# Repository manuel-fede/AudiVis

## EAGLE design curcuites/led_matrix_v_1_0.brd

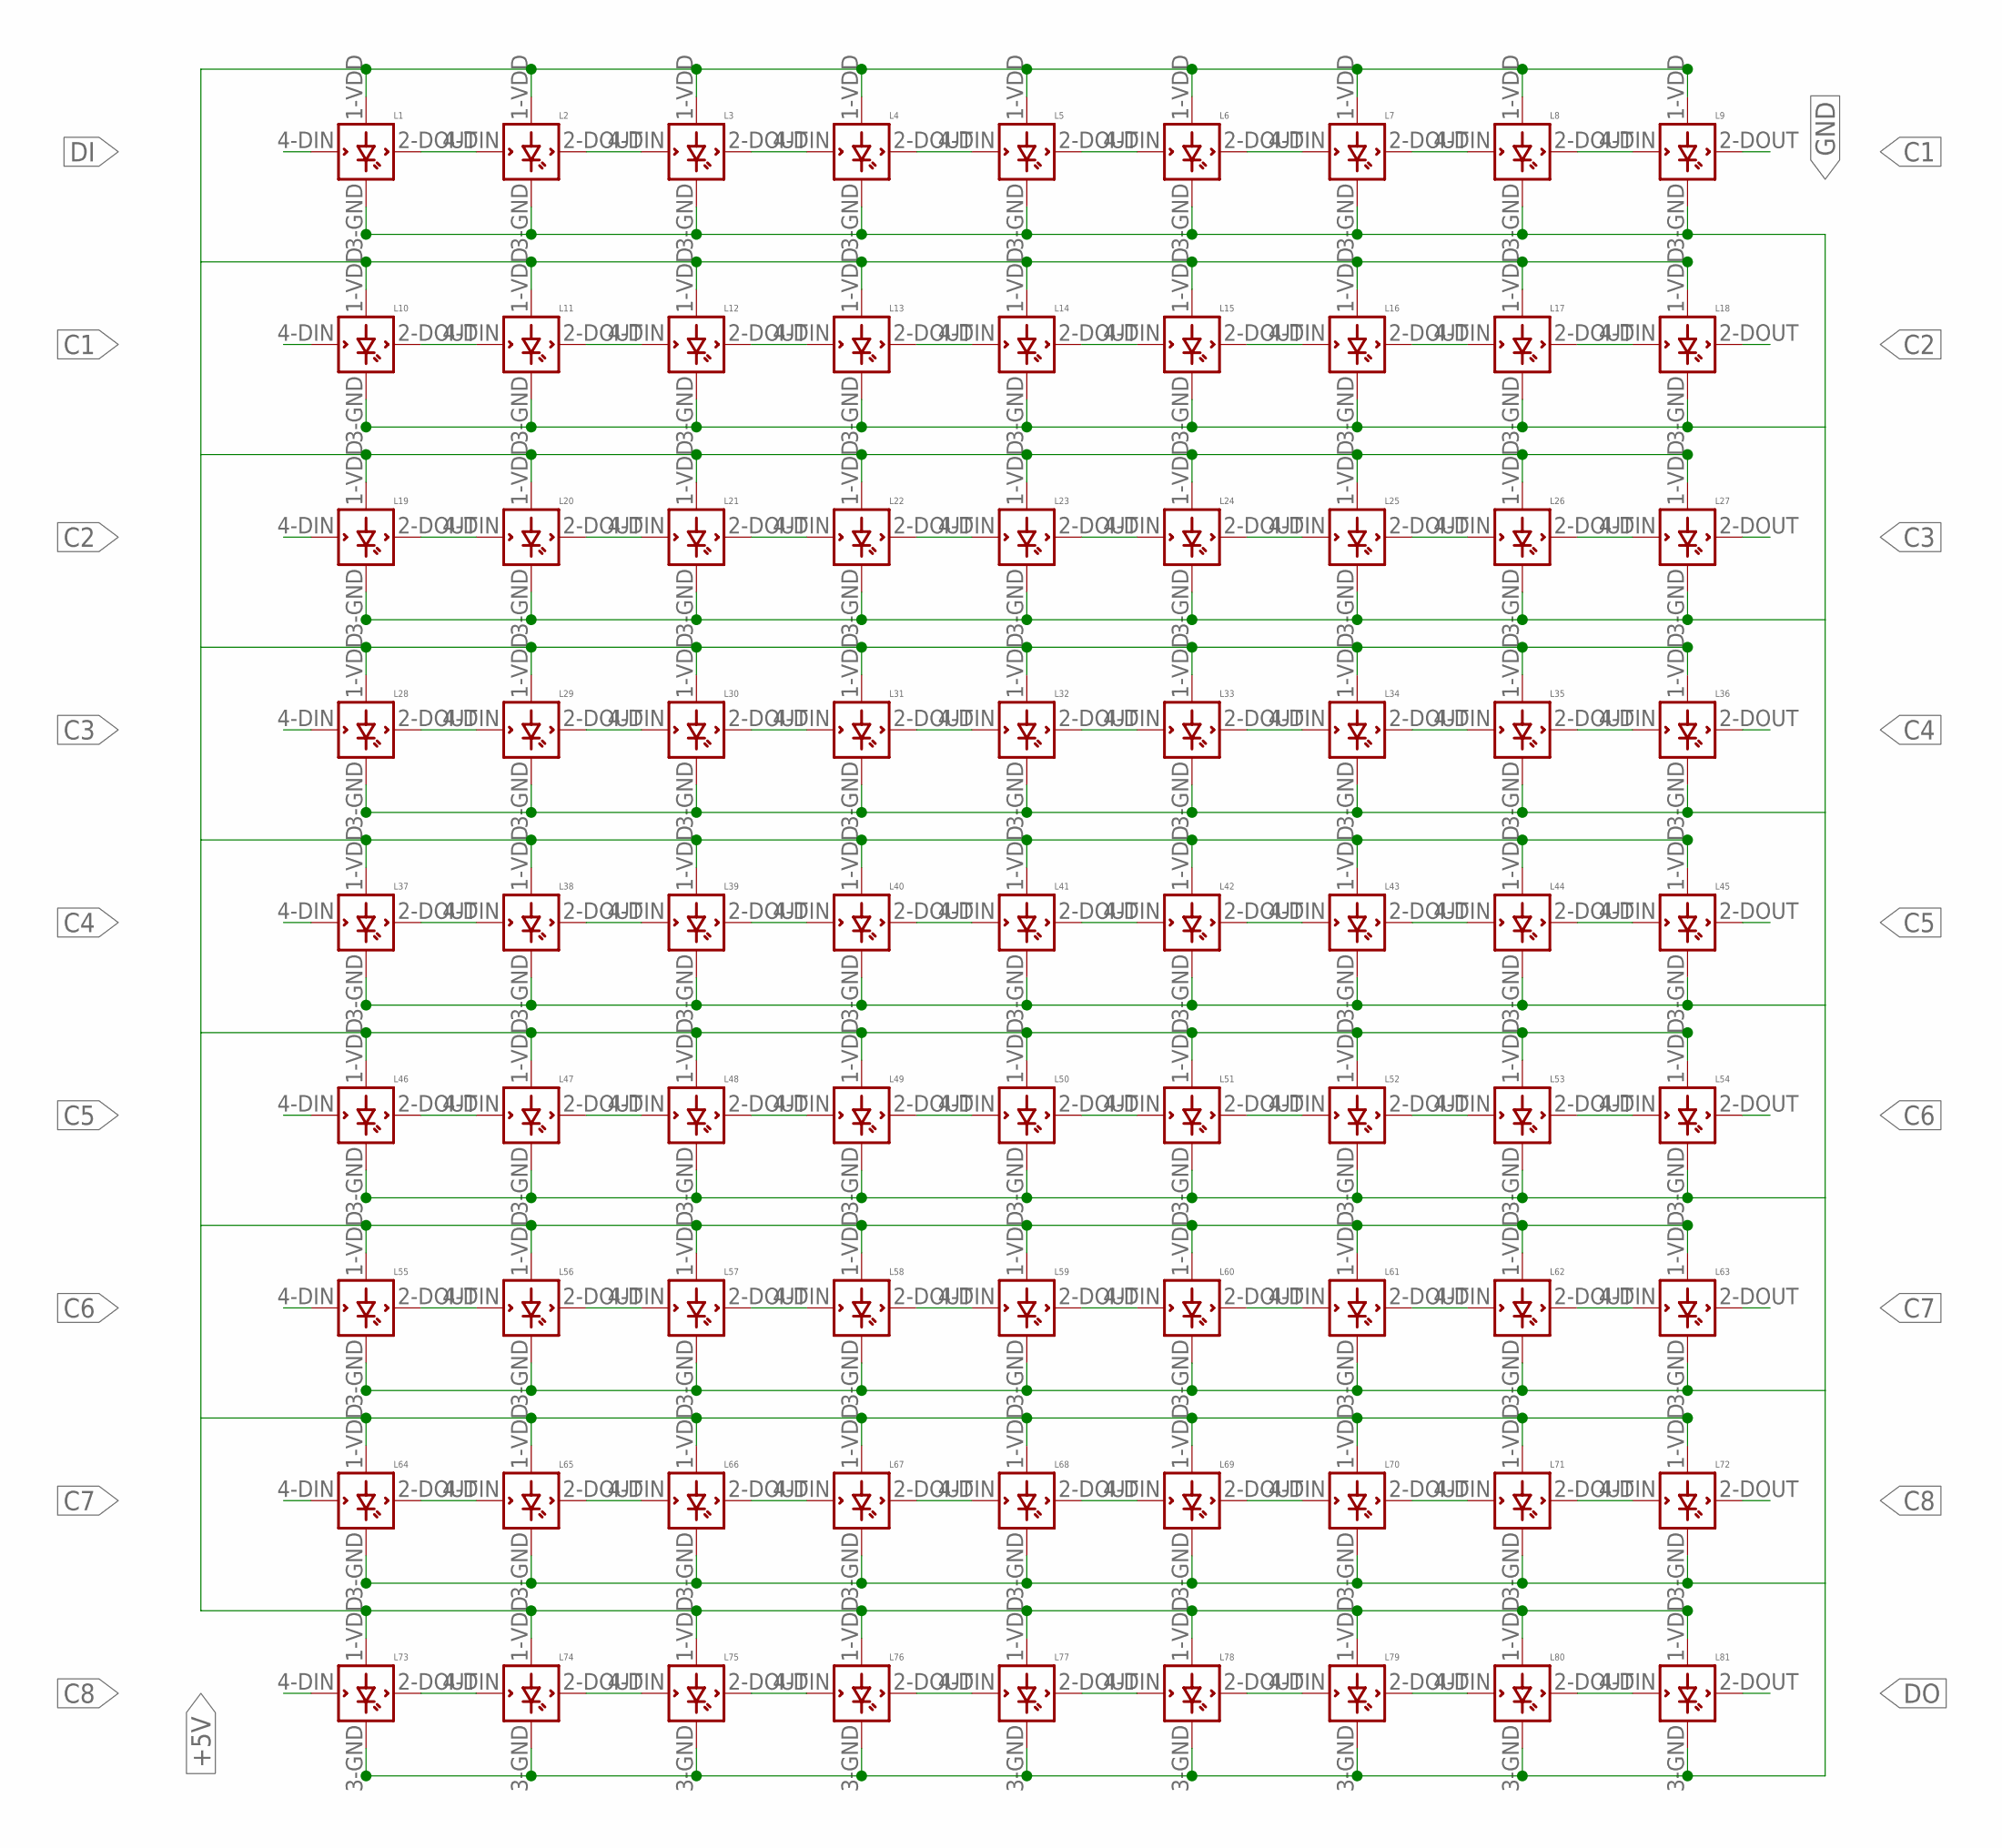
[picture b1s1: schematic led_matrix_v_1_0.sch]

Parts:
L1, L2, L3, L4, L5, L6, L7, L8, L9, L10, L11, L12, L13, L14, L15, L16, L17, L18, L19, L20, L21, L22, L23, L24, L25, L26, L27, L28, L29, L30, L31, L32, L33, L34, L35, L36, L37, L38, L39, L40, L41, L42, L43, L44, L45, L46, L47, L48, L49, L50, L51, L52, L53, L54, L55, L56, L57, L58, L59, L60, L61, L62, L63, L64, L65, L66, L67, L68, L69, L70, L71, L72, L73, L74, L75, L76, L77, L78, L79, L80, L81: WS2812B

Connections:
+5V: L1.1-VDD (VDD), L2.1-VDD (VDD), L3.1-VDD (VDD), L4.1-VDD (VDD), L5.1-VDD (VDD), L6.1-VDD (VDD), L7.1-VDD (VDD), L8.1-VDD (VDD), L9.1-VDD (VDD), L10.1-VDD (VDD), L11.1-VDD (VDD), L12.1-VDD (VDD), L13.1-VDD (VDD), L14.1-VDD (VDD), L15.1-VDD (VDD), L16.1-VDD (VDD), L17.1-VDD (VDD), L18.1-VDD (VDD), L19.1-VDD (VDD), L20.1-VDD (VDD), L21.1-VDD (VDD), L22.1-VDD (VDD), L23.1-VDD (VDD), L24.1-VDD (VDD), L25.1-VDD (VDD), L26.1-VDD (VDD), L27.1-VDD (VDD), L28.1-VDD (VDD), L29.1-VDD (VDD), L30.1-VDD (VDD), L31.1-VDD (VDD), L32.1-VDD (VDD), L33.1-VDD (VDD), L34.1-VDD (VDD), L35.1-VDD (VDD), L36.1-VDD (VDD), L37.1-VDD (VDD), L38.1-VDD (VDD), L39.1-VDD (VDD), L40.1-VDD (VDD), L41.1-VDD (VDD), L42.1-VDD (VDD), L43.1-VDD (VDD), L44.1-VDD (VDD), L45.1-VDD (VDD), L46.1-VDD (VDD), L47.1-VDD (VDD), L48.1-VDD (VDD), L49.1-VDD (VDD), L50.1-VDD (VDD), L51.1-VDD (VDD), L52.1-VDD (VDD), L53.1-VDD (VDD), L54.1-VDD (VDD), L55.1-VDD (VDD), L56.1-VDD (VDD), L57.1-VDD (VDD), L58.1-VDD (VDD), L59.1-VDD (VDD), L60.1-VDD (VDD), L61.1-VDD (VDD), L62.1-VDD (VDD), L63.1-VDD (VDD), L64.1-VDD (VDD), L65.1-VDD (VDD), L66.1-VDD (VDD), L67.1-VDD (VDD), L68.1-VDD (VDD), L69.1-VDD (VDD), L70.1-VDD (VDD), L71.1-VDD (VDD), L72.1-VDD (VDD), L73.1-VDD (VDD), L74.1-VDD (VDD), L75.1-VDD (VDD), L76.1-VDD (VDD), L77.1-VDD (VDD), L78.1-VDD (VDD), L79.1-VDD (VDD), L80.1-VDD (VDD), L81.1-VDD (VDD)
C1: L9.2-DOUT (DOUT), L10.4-DIN (DIN)
C2: L18.2-DOUT (DOUT), L19.4-DIN (DIN)
C3: L27.2-DOUT (DOUT), L28.4-DIN (DIN)
C4: L36.2-DOUT (DOUT), L37.4-DIN (DIN)
C5: L45.2-DOUT (DOUT), L46.4-DIN (DIN)
C6: L54.2-DOUT (DOUT), L55.4-DIN (DIN)
C7: L63.2-DOUT (DOUT), L64.4-DIN (DIN)
C8: L72.2-DOUT (DOUT), L73.4-DIN (DIN)
DI: L1.4-DIN (DIN)
DO: L81.2-DOUT (DOUT)
GND: L1.3-GND (GND), L2.3-GND (GND), L3.3-GND (GND), L4.3-GND (GND), L5.3-GND (GND), L6.3-GND (GND), L7.3-GND (GND), L8.3-GND (GND), L9.3-GND (GND), L10.3-GND (GND), L11.3-GND (GND), L12.3-GND (GND), L13.3-GND (GND), L14.3-GND (GND), L15.3-GND (GND), L16.3-GND (GND), L17.3-GND (GND), L18.3-GND (GND), L19.3-GND (GND), L20.3-GND (GND), L21.3-GND (GND), L22.3-GND (GND), L23.3-GND (GND), L24.3-GND (GND), L25.3-GND (GND), L26.3-GND (GND), L27.3-GND (GND), L28.3-GND (GND), L29.3-GND (GND), L30.3-GND (GND), L31.3-GND (GND), L32.3-GND (GND), L33.3-GND (GND), L34.3-GND (GND), L35.3-GND (GND), L36.3-GND (GND), L37.3-GND (GND), L38.3-GND (GND), L39.3-GND (GND), L40.3-GND (GND), L41.3-GND (GND), L42.3-GND (GND), L43.3-GND (GND), L44.3-GND (GND), L45.3-GND (GND), L46.3-GND (GND), L47.3-GND (GND), L48.3-GND (GND), L49.3-GND (GND), L50.3-GND (GND), L51.3-GND (GND), L52.3-GND (GND), L53.3-GND (GND), L54.3-GND (GND), L55.3-GND (GND), L56.3-GND (GND), L57.3-GND (GND), L58.3-GND (GND), L59.3-GND (GND), L60.3-GND (GND), L61.3-GND (GND), L62.3-GND (GND), L63.3-GND (GND), L64.3-GND (GND), L65.3-GND (GND), L66.3-GND (GND), L67.3-GND (GND), L68.3-GND (GND), L69.3-GND (GND), L70.3-GND (GND), L71.3-GND (GND), L72.3-GND (GND), L73.3-GND (GND), L74.3-GND (GND), L75.3-GND (GND), L76.3-GND (GND), L77.3-GND (GND), L78.3-GND (GND), L79.3-GND (GND), L80.3-GND (GND), L81.3-GND (GND)
unnamed: L10.2-DOUT (DOUT), L11.4-DIN (DIN)
unnamed: L2.2-DOUT (DOUT), L3.4-DIN (DIN)
unnamed: L3.2-DOUT (DOUT), L4.4-DIN (DIN)
unnamed: L11.2-DOUT (DOUT), L12.4-DIN (DIN)
unnamed: L4.2-DOUT (DOUT), L5.4-DIN (DIN)
unnamed: L12.2-DOUT (DOUT), L13.4-DIN (DIN)
unnamed: L1.2-DOUT (DOUT), L2.4-DIN (DIN)
unnamed: L5.2-DOUT (DOUT), L6.4-DIN (DIN)
unnamed: L6.2-DOUT (DOUT), L7.4-DIN (DIN)
unnamed: L7.2-DOUT (DOUT), L8.4-DIN (DIN)
unnamed: L8.2-DOUT (DOUT), L9.4-DIN (DIN)
unnamed: L13.2-DOUT (DOUT), L14.4-DIN (DIN)
unnamed: L14.2-DOUT (DOUT), L15.4-DIN (DIN)
unnamed: L15.2-DOUT (DOUT), L16.4-DIN (DIN)
unnamed: L16.2-DOUT (DOUT), L17.4-DIN (DIN)
unnamed: L17.2-DOUT (DOUT), L18.4-DIN (DIN)
unnamed: L19.2-DOUT (DOUT), L20.4-DIN (DIN)
unnamed: L20.2-DOUT (DOUT), L21.4-DIN (DIN)
unnamed: L21.2-DOUT (DOUT), L22.4-DIN (DIN)
unnamed: L22.2-DOUT (DOUT), L23.4-DIN (DIN)
unnamed: L23.2-DOUT (DOUT), L24.4-DIN (DIN)
unnamed: L24.2-DOUT (DOUT), L25.4-DIN (DIN)
unnamed: L25.2-DOUT (DOUT), L26.4-DIN (DIN)
unnamed: L26.2-DOUT (DOUT), L27.4-DIN (DIN)
unnamed: L28.2-DOUT (DOUT), L29.4-DIN (DIN)
unnamed: L29.2-DOUT (DOUT), L30.4-DIN (DIN)
unnamed: L30.2-DOUT (DOUT), L31.4-DIN (DIN)
unnamed: L31.2-DOUT (DOUT), L32.4-DIN (DIN)
unnamed: L32.2-DOUT (DOUT), L33.4-DIN (DIN)
unnamed: L33.2-DOUT (DOUT), L34.4-DIN (DIN)
unnamed: L34.2-DOUT (DOUT), L35.4-DIN (DIN)
unnamed: L35.2-DOUT (DOUT), L36.4-DIN (DIN)
unnamed: L37.2-DOUT (DOUT), L38.4-DIN (DIN)
unnamed: L38.2-DOUT (DOUT), L39.4-DIN (DIN)
unnamed: L39.2-DOUT (DOUT), L40.4-DIN (DIN)
unnamed: L40.2-DOUT (DOUT), L41.4-DIN (DIN)
unnamed: L41.2-DOUT (DOUT), L42.4-DIN (DIN)
unnamed: L42.2-DOUT (DOUT), L43.4-DIN (DIN)
unnamed: L43.2-DOUT (DOUT), L44.4-DIN (DIN)
unnamed: L44.2-DOUT (DOUT), L45.4-DIN (DIN)
unnamed: L46.2-DOUT (DOUT), L47.4-DIN (DIN)
unnamed: L47.2-DOUT (DOUT), L48.4-DIN (DIN)
unnamed: L48.2-DOUT (DOUT), L49.4-DIN (DIN)
unnamed: L49.2-DOUT (DOUT), L50.4-DIN (DIN)
unnamed: L50.2-DOUT (DOUT), L51.4-DIN (DIN)
unnamed: L51.2-DOUT (DOUT), L52.4-DIN (DIN)
unnamed: L52.2-DOUT (DOUT), L53.4-DIN (DIN)
unnamed: L53.2-DOUT (DOUT), L54.4-DIN (DIN)
unnamed: L55.2-DOUT (DOUT), L56.4-DIN (DIN)
unnamed: L56.2-DOUT (DOUT), L57.4-DIN (DIN)
unnamed: L57.2-DOUT (DOUT), L58.4-DIN (DIN)
unnamed: L58.2-DOUT (DOUT), L59.4-DIN (DIN)
unnamed: L59.2-DOUT (DOUT), L60.4-DIN (DIN)
unnamed: L60.2-DOUT (DOUT), L61.4-DIN (DIN)
unnamed: L61.2-DOUT (DOUT), L62.4-DIN (DIN)
unnamed: L62.2-DOUT (DOUT), L63.4-DIN (DIN)
unnamed: L64.2-DOUT (DOUT), L65.4-DIN (DIN)
unnamed: L65.2-DOUT (DOUT), L66.4-DIN (DIN)
unnamed: L66.2-DOUT (DOUT), L67.4-DIN (DIN)
unnamed: L67.2-DOUT (DOUT), L68.4-DIN (DIN)
unnamed: L68.2-DOUT (DOUT), L69.4-DIN (DIN)
unnamed: L69.2-DOUT (DOUT), L70.4-DIN (DIN)
unnamed: L70.2-DOUT (DOUT), L71.4-DIN (DIN)
unnamed: L71.2-DOUT (DOUT), L72.4-DIN (DIN)
unnamed: L73.2-DOUT (DOUT), L74.4-DIN (DIN)
unnamed: L74.2-DOUT (DOUT), L75.4-DIN (DIN)
unnamed: L75.2-DOUT (DOUT), L76.4-DIN (DIN)
unnamed: L76.2-DOUT (DOUT), L77.4-DIN (DIN)
unnamed: L77.2-DOUT (DOUT), L78.4-DIN (DIN)
unnamed: L78.2-DOUT (DOUT), L79.4-DIN (DIN)
unnamed: L79.2-DOUT (DOUT), L80.4-DIN (DIN)
unnamed: L80.2-DOUT (DOUT), L81.4-DIN (DIN)

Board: 2 copper layers, 81 parts (81 on the bottom side), 82 nets, no tracks yet.

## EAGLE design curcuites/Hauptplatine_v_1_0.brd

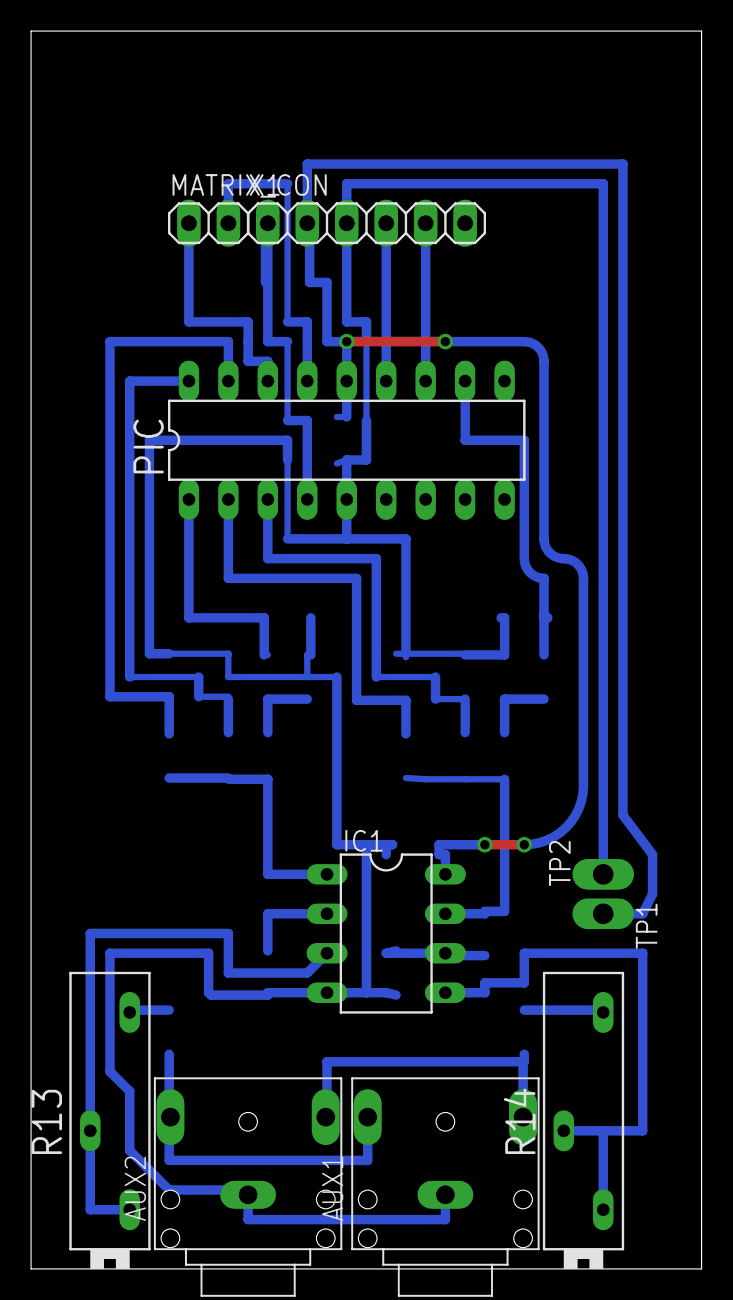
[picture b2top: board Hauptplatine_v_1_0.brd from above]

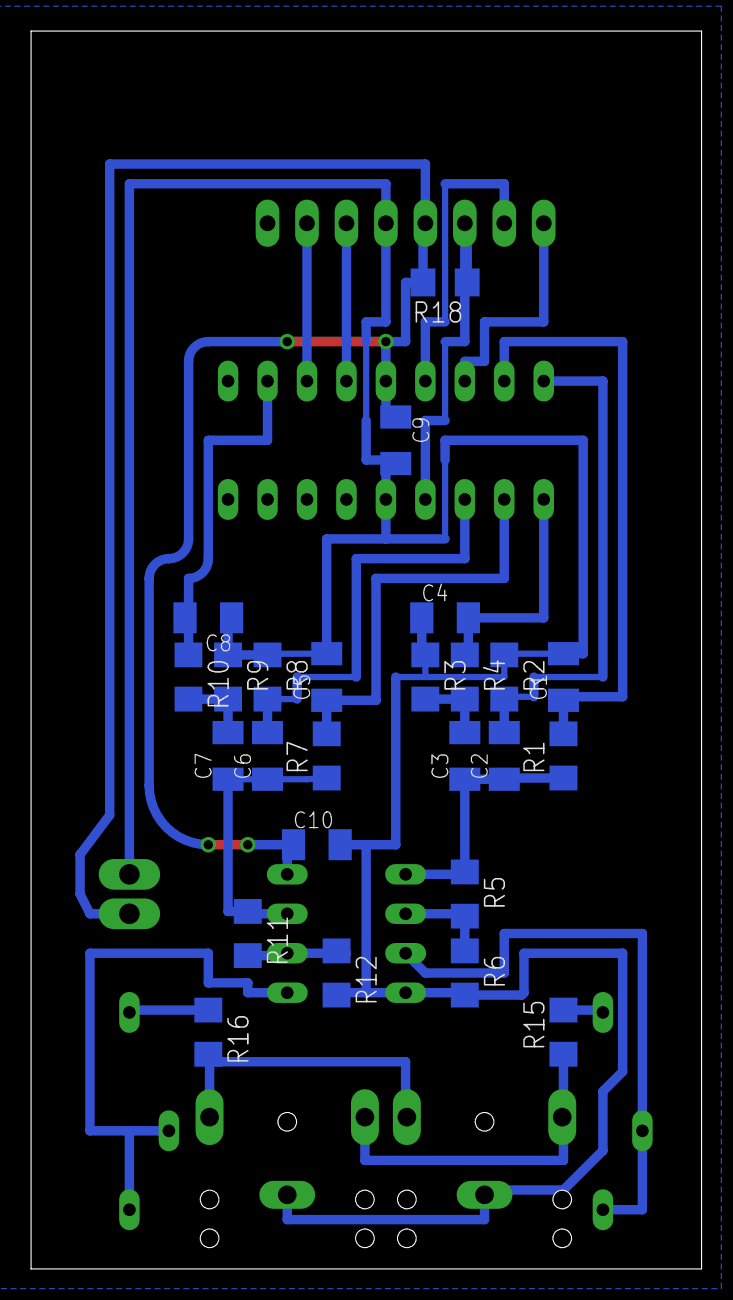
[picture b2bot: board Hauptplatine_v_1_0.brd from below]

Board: 2 copper layers, 43.2 x 79.7 mm, 35 parts (25 on the bottom side), 25 nets.

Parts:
AUX1, AUX2: 1501_03KLB3MM5; KLB3MM5
C1, C3, C5, C7: 470n; C1206
C2, C4, C6, C8: 68n; C1206
C9, C10: 22n; C1206
IC1: LM4558N; DIL08
MATRIX_CON: 1X02
PIC: PIC16F1826/27P; DIL18
R1, R2, R3, R4, R7, R8, R9, R10, R15, R16: 1k; R_SMD1206
R5, R11: 10k; R_SMD1206
R6, R12: 8k2; R_SMD1206
R13, R14: 10k; PT-SPIN
R18: 47k; R_SMD1206
TP1, TP2: TPPAD1-13Y; P1-13Y
X1: 0; 1X06

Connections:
+5V: C9.1, C10.1, IC1.8, PIC.14, R18.2, TP1.TP, X1.2_VDD
AUX_IN_2: IC1.5, R14.A, R14.S
GND: AUX1.P1, AUX2.P1, C1.2, C4.1, C5.2, C8.1, C9.2, C10.2, IC1.4, PIC.5, R2.1, R3.1, R6.2, R8.1, R9.1, R12.2, TP2.TP, X1.3_VSS
unnamed: C3.2, R3.2, R4.2
unnamed: PIC.4, R18.1, X1.1_MCLR/VPP
unnamed: MATRIX_CON.2, PIC.15
unnamed: IC1.2, R5.2, R6.1
unnamed: MATRIX_CON.1, PIC.16
unnamed: C4.2, PIC.1, R4.1
unnamed: R13.E, R15.2
unnamed: C7.2, R9.2, R10.2
unnamed: C8.2, PIC.11, R10.1
unnamed: IC1.6, R11.2, R12.1
unnamed: R14.E, R16.1
unnamed: IC1.3, R13.A, R13.S
unnamed: AUX1.P2, AUX2.P2, R16.2
unnamed: AUX1.P3, AUX2.P3, R15.1
PGC: PIC.12, X1.5_PGC
PGD: PIC.13, X1.4_PGD
WHATEVER: C2.1, C3.1, IC1.1, R1.1, R5.1
WHATEVER1: C1.1, PIC.17, R1.2
WHATEVER2: C2.2, PIC.18, R2.2
WHATEVER3: C5.1, PIC.2, R7.2
WHATEVER4: C6.1, C7.1, IC1.7, R7.1, R11.1
WHATEVER5: C6.2, PIC.3, R8.2

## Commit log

2015-11-19 init commit
2016-02-11 updated doc
